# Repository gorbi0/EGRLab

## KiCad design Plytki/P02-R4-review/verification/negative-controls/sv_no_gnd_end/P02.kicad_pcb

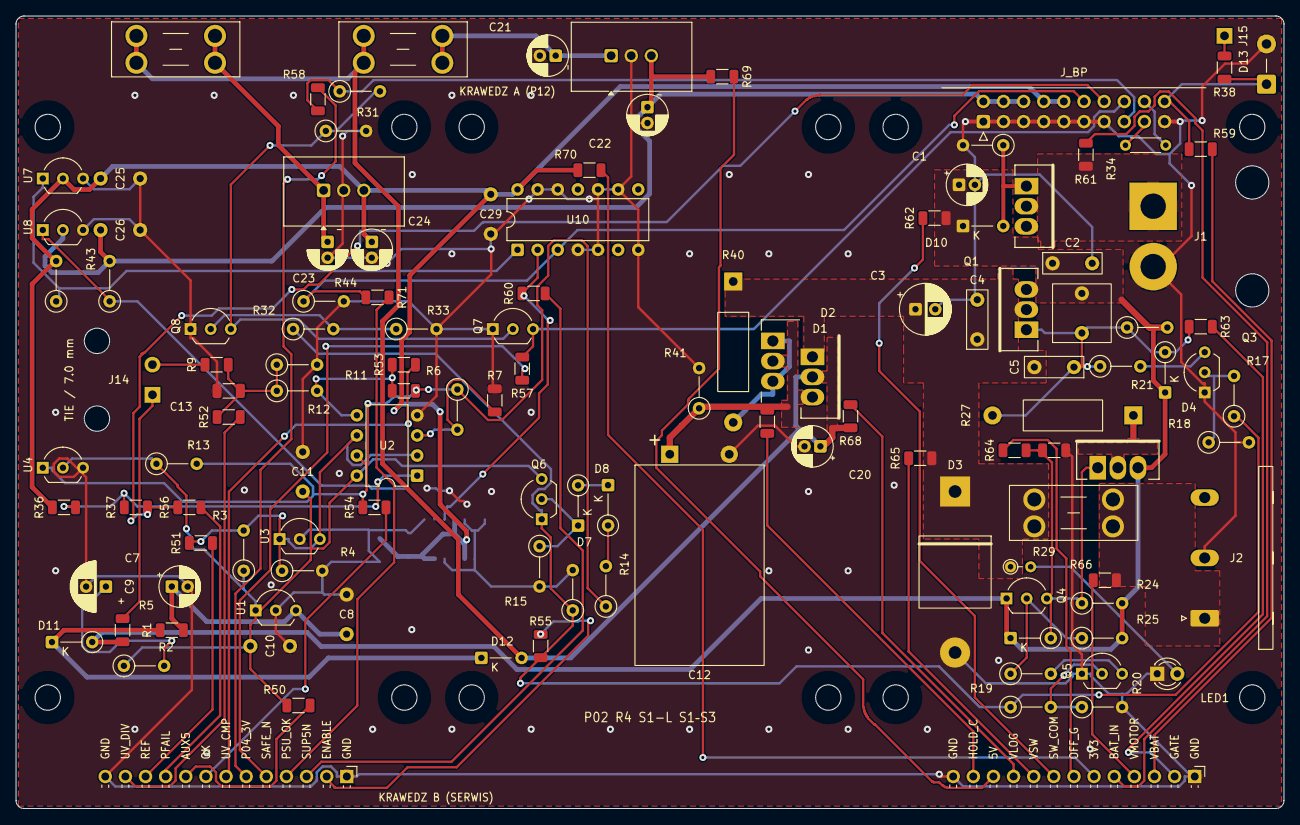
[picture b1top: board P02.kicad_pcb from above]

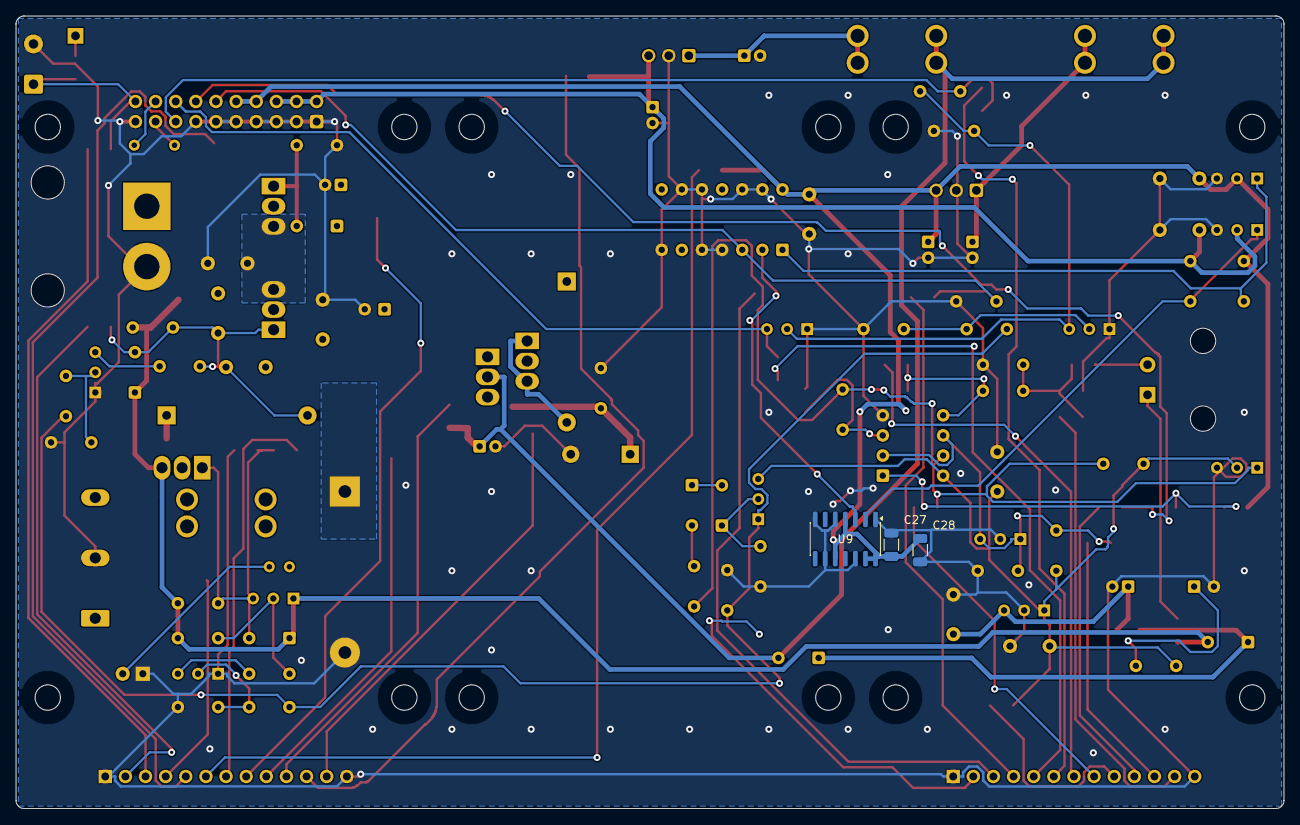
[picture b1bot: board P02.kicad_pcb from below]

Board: 2 copper layers, 160.0 x 100.0 mm, 139 parts (3 on the bottom side), 73 nets.

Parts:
C1, C21, C23: 10u; CP_Radial_D5.0mm_P2.00mm
C2, C4: 100nF; C_TDK_B32529_L7.3_W2.5_P5
C3, C9: 47u; CP_Radial_D6.3mm_P2.50mm
C5: 10nF; C_TDK_B32529_L7.3_W2.5_P5
C6: 1uF; C_WIMA_MKS2_1u100V_L7.2_W7.2_P5
C7, C20, C22, C24: 22u; CP_Radial_D5.0mm_P2.00mm
C8, C10, C11, C25, C26, C29: 100nF; C_Vishay_K15_H5_P5
C12: 2200u; CP_Radial_D16.0mm_L25mm_P7.50mm_Lying
C13: 10nF; C_1206_3216Metric
C27, C28: 100nF; C_1206_3216Metric
D1, D2: STPS20100CT; TO220_3_P2.54_Drill1.4
D3: 5KP24A; TVS_P600_P20.32
D4, D9, D10: BZX55C15; D_DO-35_SOD27_P5.08mm_Vertical_CathodeUp
D7, D8, D11, D12: 1N4148; D_DO-35_SOD27_P5.08mm_Vertical_CathodeUp
D13: P6KE24CA; D_DO-15_P5.08mm_Vertical_CathodeUp
F1: 5A; Fuseholder_Blade_Mini_Keystone_3568
F2, F3: 1A; Fuseholder_Blade_Mini_Keystone_3568
H1, H2, H3, H4, H5, H6, H7, H8, H9, H10, H11, H12: M3 NPTH
J1: BAT; Pigtail_PWR_2x2.5mm2
J2: VMOTOR; PhoenixContact_GMSTBA_2,5_3-G-7,62_1x03_P7.62mm_Horizontal
J14: PWR; Pigtail_PWR_SW_2xAWG22_T7
J15: VBAT_IN; Pigtail_VBAT_1xAWG22
J_BP: J_BP; IDC-Header_2x10_P2.54mm_Horizontal
J_SV1: J_SV1; PinHeader_1x13_P2.54mm_Horizontal
J_SV2: J_SV2; PinHeader_1x13_P2.54mm_Horizontal
LED1: GREEN 3mm; LED_D3.0mm
Q1, Q2, Q9: SUP53P06-20; TO220_3_P2.54_Drill1.4
Q3, Q5, Q6, Q7, Q8: 2N5551G; TO-92_Inline_Wide
Q4: 2N5401YBU; TO-92_Inline_Wide
R1: 47R; R_1206_3216Metric
R2: 1R; R_Axial_DIN0207_L6.3mm_D2.5mm_P5.08mm_Vertical
R3: 820R; R_Axial_DIN0207_L6.3mm_D2.5mm_P5.08mm_Vertical
R4, R10, R12, R16, R26, R30, R32, R41, R42, R43, R44: 10K; R_Axial_DIN0207_L6.3mm_D2.5mm_P5.08mm_Vertical
R5, R37, R50, R54, R55, R56, R57, R58, R60, R69, R70, R71: 1K; R_1206_3216Metric
R6, R15, R21, R24, R31, R35: 100K; R_Axial_DIN0207_L6.3mm_D2.5mm_P5.08mm_Vertical
R7: 150K; R_1206_3216Metric
R9: 41K2; R_1206_3216Metric
R11: 464K; R_1206_3216Metric
R13: 2K2; R_Axial_DIN0207_L6.3mm_D2.5mm_P5.08mm_Vertical
R14, R17, R19: 4K7; R_Axial_DIN0207_L6.3mm_D2.5mm_P5.08mm_Vertical
R18, R20, R25, R33: 47K; R_Axial_DIN0207_L6.3mm_D2.5mm_P5.08mm_Vertical
R22: 470K; R_Axial_DIN0207_L6.3mm_D2.5mm_P5.08mm_Vertical
R23: 22K; R_1206_3216Metric
R27: 10R; R_PR02_P17.78
R29: 6K8; R_Axial_DIN0204_L3.6mm_D1.6mm_P2.54mm_Vertical
R34: 0R; R_Axial_DIN0204_L3.6mm_D1.6mm_P5.08mm_Horizontal
R36, R38, R51, R52, R53, R59, R63, R64: 10K; R_1206_3216Metric
R40: 22R; R_PR02_P17.78
R61, R62, R65, R66, R67, R68: 4K7; R_1206_3216Metric
U1: LM2936Z-5.0; TO-92_Inline_Wide
U2: LM2903P; DIP-8_W7.62mm
U3: TL431BILP; TO-92_Inline_Wide
U4, U8: MCP120-450DI/TO; TO-92_Inline_Wide
U5: TSR 2-2450; Converter_DCDC_TRACO_TSR2-xxxx_THT
U6: TSR 2-2433; Converter_DCDC_TRACO_TSR2-xxxx_THT
U7: MCP120-300DI/TO; TO-92_Inline_Wide
U9: 74LVC125A; SOIC-14_3.9x8.7mm_P1.27mm
U10: SN74HC08N; DIP-14_W7.62mm

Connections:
3V3_IO: C24.1, C25.1, C27.1, C28.1, C29.1, J_BP.8, J_BP.10, R36.1, R42.2, R70.1, U6.3, U7.2, U9.4, U9.10, U9.13, U9.14, U10.14
5V_SYS: C22.1, C26.1, J_BP.2, J_BP.4, J_BP.6, R43.2, R69.1, U5.3, U8.2
/LV/P02_VIN_DC5: C21.1, F2.2, U5.1
/LV/P02_VIN_DC33: C23.1, F3.2, U6.1
/MON/P02_SUP3_N: R42.1, U7.1, U10.1
/MON/P02_SUP5_RAW: R43.1, U8.1, U9.2
/MON/VBAT_CAR: J15.1, R38.1
/P02_CH_A: D2.1, D2.3, R40.2
/P02_OFF_D: Q2.2, R27.1
/P02_ON_B: Q3.2, R17.2, R18.1
/P02_ON_COL: Q3.3, R21.2
/P02_REL_B: Q5.2, R19.2, R20.1
/P02_REL_COL: Q5.3, R26.2
/P02_REL_PB: Q4.2, R25.1, R26.1
/P02_REV_G: D10.2, Q9.1, R35.1
/SERW/P02_SV_3V3_IO: J_SV2.6, R70.2
/SERW/P02_SV_5V_SYS: J_SV2.11, R69.2
/SERW/P02_SV_AUX5: J_SV1.9, R50.2
/SERW/P02_SV_BAT_IN: J_SV2.5, R61.2
/SERW/P02_SV_ENABLE: J_SV1.2, R55.2
/SERW/P02_SV_GATE: J_SV2.2, R63.2
/SERW/P02_SV_HOLD_C: J_SV2.12, R67.2
/SERW/P02_SV_OFF_G: J_SV2.7, R64.2
/SERW/P02_SV_OK: J_SV1.8, R54.2
/SERW/P02_SV_P04_3V3: J_SV1.6, R58.2
/SERW/P02_SV_PFAIL_N: J_SV1.10, R56.2
/SERW/P02_SV_PSU_OK: J_SV1.4, R71.2
/SERW/P02_SV_REF: J_SV1.11, R51.2
/SERW/P02_SV_SAFE_N: J_SV1.5, R57.2
/SERW/P02_SV_SUP5_N: J_SV1.3, R60.2
/SERW/P02_SV_SW_COM: J_SV2.8, R62.2
/SERW/P02_SV_UV_CMP: J_SV1.7, R53.2
/SERW/P02_SV_UV_DIV: J_SV1.12, J_SV1.13, R52.2
/SERW/P02_SV_VBAT_SENSE: J_SV2.3, R59.2
/SERW/P02_SV_VLOG: J_SV2.10, R68.2
/SERW/P02_SV_VMOTOR: J_SV2.4, R66.2
/SERW/P02_SV_VSW: J_SV2.9, R65.2
/STER/P02_AUX_IN: C7.1, C8.1, R1.2, U1.3
/STER/P02_BUF_BASE: D8.1, Q6.2, R15.1
/STER/P02_BUF_D1: D7.2, R14.2
/STER/P02_BUF_D2: D7.1, D8.2
/STER/P02_C_AUX_TOP: C9.1, R2.2
/STER/P02_FAULT_B: Q7.2, Q8.3, R30.2, R31.1
/STER/P02_FAULT_REL_B: Q8.2, R32.2, R33.1
/STER/P02_LED_A: LED1.2, R29.2
/STER/P02_PFAIL_OC: R36.2, R37.1, U2.1
/STER/P02_PF_IN: R6.2, R7.1, U2.3
/STER/P02_PWR_A: J14.1, R5.2
/STER/P02_PWR_B: J14.2, R9.1
/STER/P02_V_CTRL: D11.1, D12.1, R1.1
GND: C1.2, C2.2, C3.2, C4.2, C7.2, C8.2, C9.2, C10.2, C11.2, C12.2, C13.2, C20.2, C21.2, C22.2, C23.2, C24.2, C25.2, C26.2, C27.2, C28.2, C29.2, D3.2, D13.2, J1.2, J2.2, J_BP.1, J_BP.3, J_BP.5, J_BP.7, J_BP.9, J_BP.11, J_BP.13, J_BP.19, J_SV1.1, J_SV2.1, J_SV2.13, LED1.1, Q3.1, Q5.1, Q7.1, Q8.1, R4.2, R7.2, R10.2, R15.2, R16.2, R18.2, R20.2, R23.2, R31.2, R33.2, R35.2, R41.2, R44.2, U1.2, U2.4, U3.2, U4.3, U5.2, U6.2, U7.3, U8.3, U9.1, U9.5, U9.7, U9.9, U9.12, U10.4, U10.5, U10.7, U10.9, U10.10, U10.12, U10.13
P02_AUX5: C10.1, C11.1, Q6.3, R2.1, R3.1, R13.1, R50.1, U1.1, U2.8, U4.2
P02_BAT_IN: J1.1, Q9.2, R61.1
P02_ENABLE: Q6.1, R16.1, R17.1, R19.1, R32.1, R55.1
P02_GATE: C5.1, C6.1, D4.2, Q1.1, R21.1, R22.1, R27.2, R63.1
P02_HOLD_C: C12.1, D1.3, D2.2, R41.1, R67.1
P02_OFF_G: D9.2, Q2.1, Q4.3, R23.1, R24.1, R64.1
P02_OK: R6.1, R11.1, R13.2, R14.1, R54.1, U2.7, U4.1
P02_REF: R3.2, R4.1, R51.1, U2.2, U2.6, U3.1, U3.3
P02_SUP5_N: R60.1, U9.3, U10.2
P02_SW_COM: C1.1, C2.1, C6.2, D4.1, D9.1, D10.1, D11.2, Q1.3, Q2.3, Q4.1, Q9.3, R5.1, R22.2, R24.2, R25.2, R62.1
P02_UV_CMP: R11.2, R12.2, R53.1, U2.5
P02_UV_DIV: C13.1, R9.2, R10.1, R12.1, R52.1
P02_VLOG: C20.1, D1.2, D12.2, F2.1, F3.1, R68.1
P02_VSW: C3.1, C4.1, C5.2, D1.1, D3.1, F1.1, Q1.2, R29.1, R40.1, R65.1
P04_3V3: J_BP.15, R30.1, R58.1
PFAIL_N: J_BP.14, R37.2, R56.1
PG_LINK: J_BP.18, R34.2
PG_SEND: J_BP.17, R34.1
PSU_OK: J_BP.12, R44.1, R71.1, U10.3
SAFE_N: J_BP.16, Q7.3, R57.1
VBAT_SENSE: D13.1, J_BP.20, R38.2, R59.1
VMOTOR: F1.2, J2.1, R66.1

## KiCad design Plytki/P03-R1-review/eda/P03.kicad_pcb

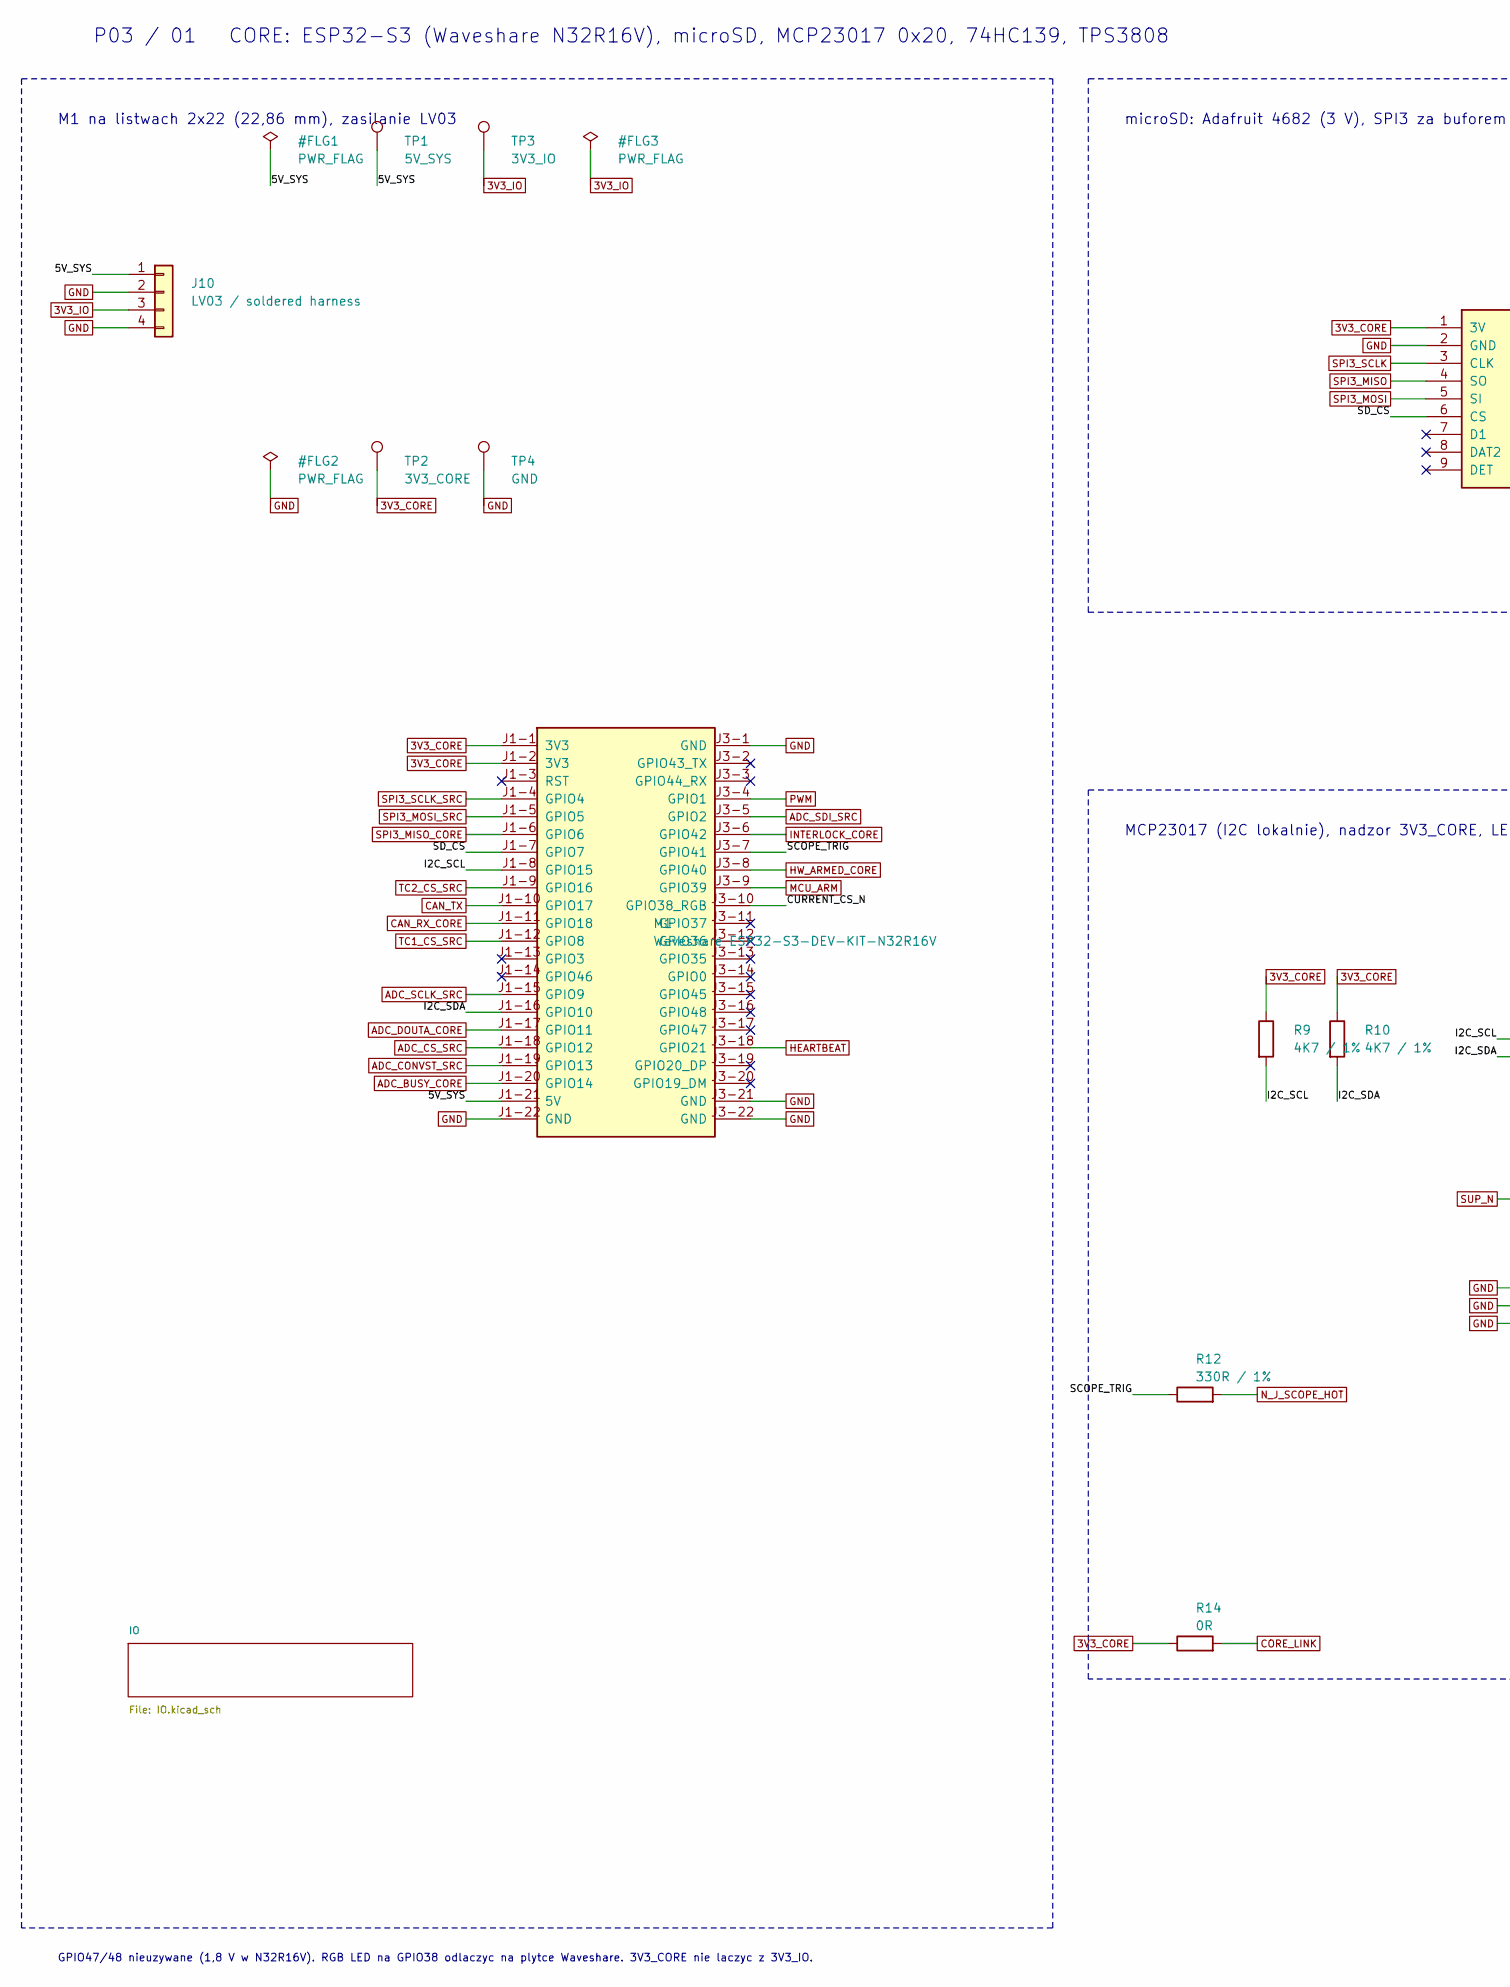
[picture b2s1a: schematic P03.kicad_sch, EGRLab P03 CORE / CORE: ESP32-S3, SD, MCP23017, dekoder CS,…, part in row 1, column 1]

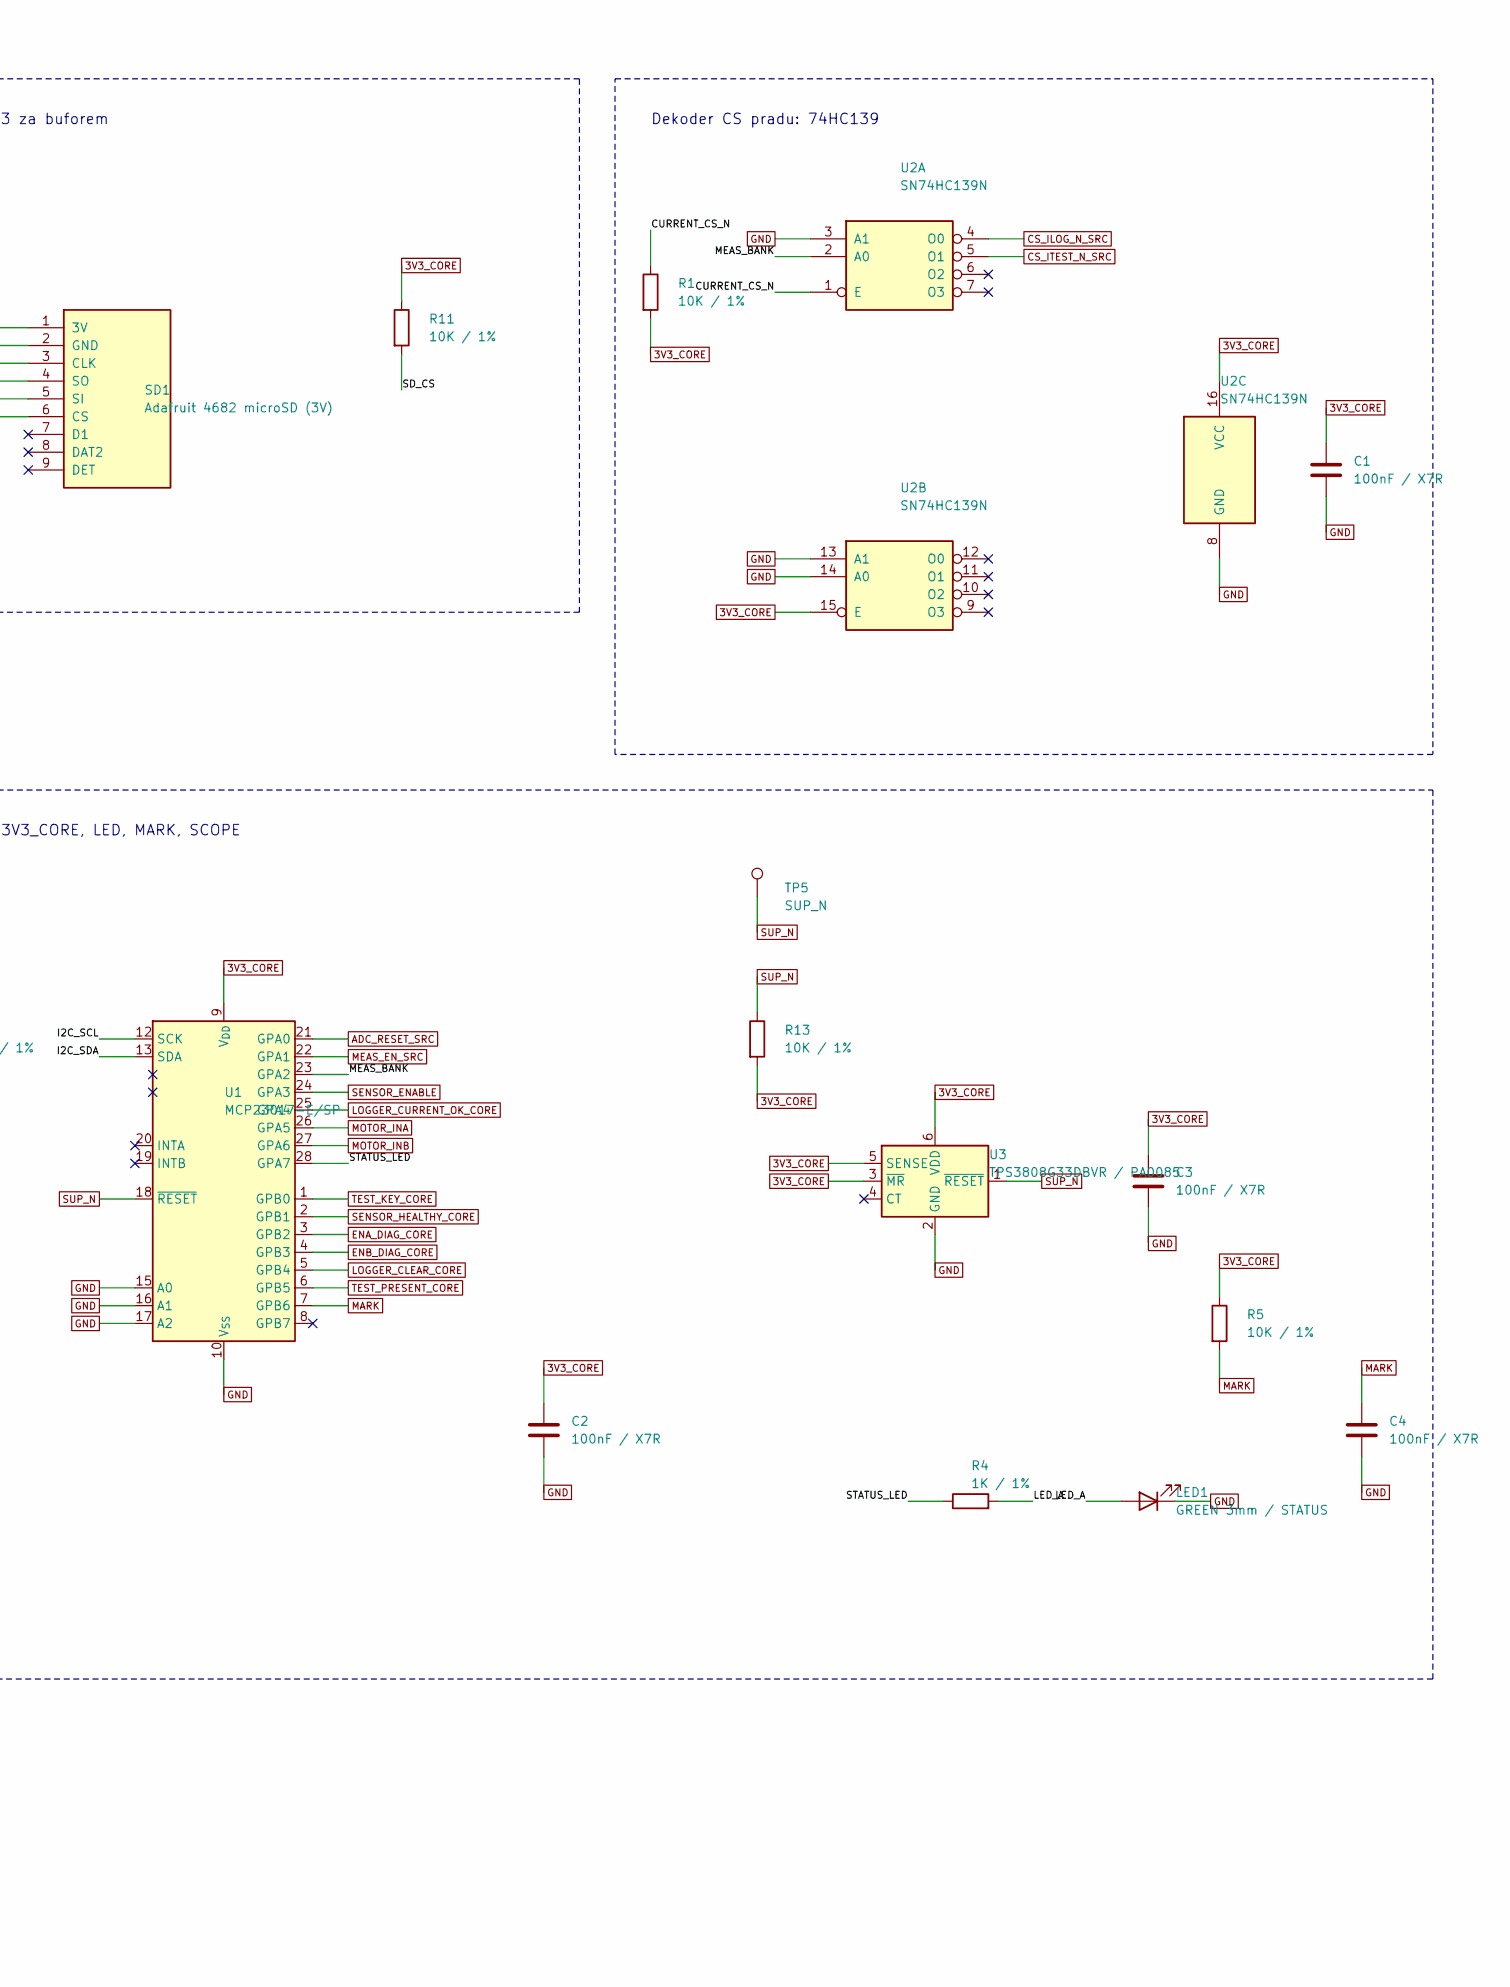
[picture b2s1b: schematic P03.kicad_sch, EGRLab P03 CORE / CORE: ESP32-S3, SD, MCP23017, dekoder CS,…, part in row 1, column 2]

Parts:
C1, C2, C3, C4: 100nF / X7R; C_Vishay_K15_H5_P5; MPN K104K15X7RF53H5
J10: LV03 / soldered harness; Pigtail_LV_4xAWG22_P3.81; MPN PCB termination; H_LV03 from P02 J3
LED1: GREEN 3mm / STATUS; LED_D3.0mm; MPN L-934GD
M1: Waveshare ESP32-S3-DEV-KIT-N32R16V; Waveshare_ESP32-S3-DEV-KIT_2x22_W22.86; MPN owned (Waveshare ESP32-S3-DEV-KIT-N32R1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
R1, R5, R11, R13: 10K / 1%; R_Axial_DIN0207_L6.3mm_D2.5mm_P10.16mm_Horizontal; MPN MF0207FTE-10K
R4: 1K / 1%; R_Axial_DIN0207_L6.3mm_D2.5mm_P10.16mm_Horizontal; MPN MF0207FTE-1K
R9, R10: 4K7 / 1%; R_Axial_DIN0207_L6.3mm_D2.5mm_P10.16mm_Horizontal; MPN MF0207FTE-4K7
R12: 330R / 1%; R_Axial_DIN0207_L6.3mm_D2.5mm_P10.16mm_Horizontal; MPN MF0207FTE-330R
R14: 0R; R_Axial_DIN0207_L6.3mm_D2.5mm_P10.16mm_Horizontal; MPN ZOR-25-R-52-0R (or wire link)
SD1: Adafruit 4682 microSD (3V); Adafruit_4682_microSD_1x09; MPN Adafruit 4682 on a 1x9 female header + 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
TP1: 5V_SYS; TestPad_1; MPN PCB test pad
TP2: 3V3_CORE; TestPad_1; MPN PCB test pad
TP3: 3V3_IO; TestPad_1; MPN PCB test pad
TP4: GND; TestPad_1; MPN PCB test pad
TP5: SUP_N; TestPad_1; MPN PCB test pad
U1: MCP23017-E/SP; DIP-28_W7.62mm; MPN MCP23017-E/SP
U2: SN74HC139N; DIP-16_W7.62mm; MPN SN74HC139N
U3: TPS3808G33DBVR / PA0085; Adapter_SOT23-6_DIP6_W15.24_ChipQuik_PA0085; MPN TPS3808G33DBVR on Chip Quik PA0085

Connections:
3V3_CORE: C1.1, C2.1, C3.1, M1.J1-1 (3V3), M1.J1-2 (3V3), R1.2, R5.1, R9.1, R10.1, R11.1, R13.2, R14.1, SD1.1 (3V), TP2.1, U1.9 (V_{DD}), U2.15 (E), U2.16 (VCC), U3.3 (~MR), U3.5 (SENSE), U3.6 (VDD); also elsewhere on the board
3V3_IO: J10.3, TP3.1; also elsewhere on the board
/5V_SYS: J10.1, M1.J1-21 (5V), TP1.1
/CURRENT_CS_N: M1.J3-10 (GPIO38_RGB), R1.1, U2.1 (E)
/I2C_SCL: M1.J1-8 (GPIO15), R9.2, U1.12 (SCK)
/I2C_SDA: M1.J1-16 (GPIO10), R10.2, U1.13 (SDA)
/LED_A: LED1.2 (A), R4.2
/MEAS_BANK: U1.23 (GPA2), U2.2 (A0)
/SCOPE_TRIG: M1.J3-7 (GPIO41), R12.1
/SD_CS: M1.J1-7 (GPIO7), R11.2, SD1.6 (CS)
/STATUS_LED: R4.1, U1.28 (GPA7)
ADC_BUSY_CORE: M1.J1-20 (GPIO14); also elsewhere on the board
ADC_CONVST_SRC: M1.J1-19 (GPIO13); also elsewhere on the board
ADC_CS_SRC: M1.J1-18 (GPIO12); also elsewhere on the board
ADC_DOUTA_CORE: M1.J1-17 (GPIO11); also elsewhere on the board
ADC_RESET_SRC: U1.21 (GPA0); also elsewhere on the board
ADC_SCLK_SRC: M1.J1-15 (GPIO9); also elsewhere on the board
ADC_SDI_SRC: M1.J3-5 (GPIO2); also elsewhere on the board
CAN_RX_CORE: M1.J1-11 (GPIO18); also elsewhere on the board
CAN_TX: M1.J1-10 (GPIO17); also elsewhere on the board
CORE_LINK: R14.2; also elsewhere on the board
CS_ILOG_N_SRC: U2.4 (O0); also elsewhere on the board
CS_ITEST_N_SRC: U2.5 (O1); also elsewhere on the board
ENA_DIAG_CORE: U1.3 (GPB2); also elsewhere on the board
ENB_DIAG_CORE: U1.4 (GPB3); also elsewhere on the board
GND: C1.2, C2.2, C3.2, C4.2, J10.2, J10.4, LED1.1 (K), M1.J1-22 (GND), M1.J3-1 (GND), M1.J3-21 (GND), M1.J3-22 (GND), SD1.2 (GND), TP4.1, U1.10 (V_{SS}), U1.15 (A0), U1.16 (A1), U1.17 (A2), U2.3 (A1), U2.8 (GND), U2.13 (A1), U2.14 (A0), U3.2 (GND); also elsewhere on the board
HEARTBEAT: M1.J3-18 (GPIO21); also elsewhere on the board
HW_ARMED_CORE: M1.J3-8 (GPIO40); also elsewhere on the board
INTERLOCK_CORE: M1.J3-6 (GPIO42); also elsewhere on the board
LOGGER_CLEAR_CORE: U1.5 (GPB4); also elsewhere on the board
LOGGER_CURRENT_OK_CORE: U1.25 (GPA4); also elsewhere on the board
MARK: C4.1, R5.2, U1.7 (GPB6); also elsewhere on the board
MCU_ARM: M1.J3-9 (GPIO39); also elsewhere on the board
MEAS_EN_SRC: U1.22 (GPA1); also elsewhere on the board
MOTOR_INA: U1.26 (GPA5); also elsewhere on the board
MOTOR_INB: U1.27 (GPA6); also elsewhere on the board
N_J_SCOPE_HOT: R12.2; also elsewhere on the board
PWM: M1.J3-4 (GPIO1); also elsewhere on the board
SENSOR_ENABLE: U1.24 (GPA3); also elsewhere on the board
SENSOR_HEALTHY_CORE: U1.2 (GPB1); also elsewhere on the board
SPI3_MISO: SD1.4 (SO); also elsewhere on the board
SPI3_MISO_CORE: M1.J1-6 (GPIO6); also elsewhere on the board
SPI3_MOSI: SD1.5 (SI); also elsewhere on the board
SPI3_MOSI_SRC: M1.J1-5 (GPIO5); also elsewhere on the board
SPI3_SCLK: SD1.3 (CLK); also elsewhere on the board
SPI3_SCLK_SRC: M1.J1-4 (GPIO4); also elsewhere on the board
SUP_N: R13.1, TP5.1, U1.18 (~RESET), U3.1 (~RESET); also elsewhere on the board
TC1_CS_SRC: M1.J1-12 (GPIO8); also elsewhere on the board
TC2_CS_SRC: M1.J1-9 (GPIO16); also elsewhere on the board
TEST_KEY_CORE: U1.1 (GPB0); also elsewhere on the board
TEST_PRESENT_CORE: U1.6 (GPB5); also elsewhere on the board

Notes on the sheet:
P03 / 01 CORE: ESP32-S3 (Waveshare N32R16V), microSD, MCP23017 0x20, 74HC139, TPS3808
M1 na listwach 2x22 (22,86 mm), zasilanie LV03
microSD: Adafruit 4682 (3 V), SPI3 za buforem
Dekoder CS pradu: 74HC139
MCP23017 (I2C lokalnie), nadzor 3V3_CORE, LED, MARK, SCOPE
GPIO47/48 nieuzywane (1,8 V w N32R16V). RGB LED na GPIO38 odlaczyc na plytce Waveshare. 3V3_CORE nie laczyc z 3V3_IO.
